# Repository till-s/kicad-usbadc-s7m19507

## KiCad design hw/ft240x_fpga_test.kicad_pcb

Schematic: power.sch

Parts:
C1, C2, C3, C7, C8, C14, C16, C17, C63: 10u; C_1206_3216Metric; Part CNC5L1X7R1C106K160AE
C4, C5, C6: 6p8; C_0603_1608Metric; Part 885012006050
C9, C12, C13, C15, C100, C101: 100n; C_0603_1608Metric; Part GCJ188R71E104KA12D
C10, C11: 47p; C_0603_1608Metric; Part 885012006055
D7: CTS05S30; sod323; Part CTS05S30
D8: CTS05S30; sod323-special; Part CTS05S30
FB1, FB3, FB4, FB5: Ferrite_Bead MPZ1608S221A; L_0603_1608Metric; Part MPZ1608S221ATA00
J1: Ext_Power; USB_Micro-B_Molex-105017-0001; Part 1050170001
J2: USB_C_Receptacle_USB2.0; USB_C_Receptacle_GCT_USB4085_smaller_holes
J3: Jtag_Master; PinHeader_1x04_P2.54mm_Vertical
J9: Expansion; PinHeader_2x04_P2.54mm_Vertical
J11: PEN_SEL; PinHeader_2x03_P2.54mm_Vertical
JP1: Jumper_2_Open; PinHeader_1x02_P2.54mm_Vertical
JP2: Jumper_ExtSup; PinHeader_1x03_P2.54mm_Vertical
JP3: Jumper_JTAG_hack; PinHeader_1x03_P2.54mm_Vertical
L1, L3: 2u2; L_Taiyo-Yuden_NR-50xx; Part SRN8040TA-2R2Y
L2: 2.2u; L_Taiyo-Yuden_NR-50xx+bourns0703; Part SRF0703-2R2M
NT1, NT2, NT3: Net-Tie_2; NetTie-2_SMD_Pad0.5mm
Q1, Q2: Si3477; TSOT-23-6; Part Si3477
R1, R2, R3, R4, R5, R8, R9, R71, R72, R73: 100k; R_0603_1608Metric; Part RC0603FR-07100KL
R6: 200k; R_0603_1608Metric; Part ERJ-3EKF2003V
R7: 316k; R_0603_1608Metric; Part RC0603FR-07316KL
R10: 47k; R_0603_1608Metric; Part RC0603FR-07100KL
R11, R12: 27; R_0603_1608Metric; Part RC0603FR-0727RL
R29: 50; R_0402_1005Metric
R63, R64, R67, R68: 10k; R_0603_1608Metric
R65, R66, R69: 5k1; R_0603_1608Metric
R70: 35k7; R_0603_1608Metric
U1, U2, U3: TLV62569DDC; SOT-23-6; Part TLV62569PDDC
U4: FT240XS; SSOP-24_3.9x8.7mm_P0.635mm; Part FT240XS-U
U15: UTC2000; QFN-16-1EP_3x3mm_P0.5mm_EP1.75x1.75mm_ThermalVias; Part UTC2000
U16: 74LVC1G32; SOT-353_SC-70-5

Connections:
+1V2: C6.1, C16.1, C17.1, L3.1, R8.2; also elsewhere on the board
+1V8_analog: FB4.2; also elsewhere on the board
+1V8_perm: C4.1, C7.1, C9.2, JP3.1 (A), L1.1, Q1.4 (S), R6.1
+2V5: C5.1, C8.1, D8.1 (K), FB3.1, J9.6, R7.1; also elsewhere on the board
+2V5_analog: FB3.2; also elsewhere on the board
+5V: C1.1, C2.1, C3.1, C14.1, C15.2, C101.2, J9.8, JP2.2 (C), Q2.4 (S), R1.1, R71.2, U1.1 (EN), U1.4 (VIN), U2.4 (VIN), U3.4 (VIN), U4.18 (VCC), U16.5 (VCC); also elsewhere on the board
-2V5: FB5.2; also elsewhere on the board
/Power/1A5: J11.2, U15.9 (1.5A#)
/Power/3A0: J11.4, U15.10 (3A#)
/Power/PWR_EN: R72.2, R73.2, U16.4
/Power/USBD_N: R12.2, U4.14 (USBDM)
/Power/USBD_P: R11.2, U4.13 (USBDP)
/Power/USBin_N: C11.1, J2.A7 (D-), J2.B7 (D-), R12.1
/Power/USBin_P: C10.2, J2.A6 (D+), J2.B6 (D+), R11.1
EXP_IO2_1V8: J9.5; also elsewhere on the board
FIFO_CLK: R29.2; also elsewhere on the board
FIFO_D0: U4.24 (DATA0); also elsewhere on the board
FIFO_D1: U4.4 (DATA1); also elsewhere on the board
FIFO_D2: J3.3, U4.2 (DATA2); also elsewhere on the board
FIFO_D3: J3.1, U4.9 (DATA3); also elsewhere on the board
FIFO_D4: J3.4, U4.1 (DATA4); also elsewhere on the board
FIFO_D5: J3.2, U4.7 (DATA5); also elsewhere on the board
FIFO_D6: U4.8 (DATA6); also elsewhere on the board
FIFO_D7: U4.5 (DATA7); also elsewhere on the board
FIFO_RDb: U4.11 (~RD); also elsewhere on the board
FIFO_RXE: U4.21 (~RXF); also elsewhere on the board
FIFO_SIWU: U4.10 (~SI/WU); also elsewhere on the board
FIFO_TXF: U4.20 (~TXE); also elsewhere on the board
FIFO_WRb: U4.12 (~WR); also elsewhere on the board
unnamed: C4.2, R2.1, R6.2, U1.6 (FB)
unnamed: C5.2, R3.1, R7.2, U2.6 (FB)
unnamed: C6.2, R4.1, R8.1, U3.6 (FB)
unnamed: C9.1, Q1.3 (G), R72.1
unnamed: C12.2, JP3.3 (B), U4.15 (3V3OUT), U4.16 (~RESET)
unnamed: C13.2, JP3.2 (C), U4.3 (VCCIO)
unnamed: C101.1, Q2.3 (G), R73.1
unnamed: D7.1 (K), L2.1
unnamed: D8.2 (A), L2.4
unnamed: FB1.1, Q2.1 (D), Q2.2 (D), Q2.5 (D), Q2.6 (D)
unnamed: J1.1 (VBUS), JP2.1 (A)
unnamed: J2.A5 (CC1), R64.1, R66.1
unnamed: J2.B5 (CC2), R63.1, R65.1
unnamed: J11.1, J11.3, J11.5, R71.1, U16.1
unnamed: JP1.2 (B), R9.1, U16.2
unnamed: L1.2, U1.3 (SW)
unnamed: L2.2, U2.3 (SW)
unnamed: L3.2, U3.3 (SW)
unnamed: NT1.1, R2.2
unnamed: NT2.1, R3.2
unnamed: NT3.1, R4.2
unnamed: R1.2, U2.5 (PG), U3.1 (EN)
unnamed: R5.1, U1.5 (PG), U2.1 (EN)
unnamed: R9.2, R10.2, U4.23 (CBUS5)
unnamed: R29.1, U4.22 (CBUS6)
unnamed: R63.2, U15.6 (CC2)
unnamed: R64.2, U15.7 (CC1)
unnamed: R67.2, U15.3 (Enable)
unnamed: R68.2, U15.2 (CFG_SEL)
unnamed: R69.1, R70.2, U15.12 (VMON)
VBUS: C100.1, J2.A4 (VBUS), J2.A9 (VBUS), J2.B4 (VBUS), J2.B9 (VBUS), JP2.3 (B), R10.1, R67.1, R68.1, R70.1, U15.16 (VDD)
Vpp_analog: FB1.2; also elsewhere on the board

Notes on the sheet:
For external supply: - jumper ext-power to +5V - jumper gate to GND - CBUS programmed to VBUS_SENSE For bus-power: - jumper VBUS to +5V - open gate jumper - CBUS programmed to #PWREN
Alt Inductor (not same footprint): Taiyo Yuden NRS5030T2R2NMGJ
Diode in the positive 2V5 branch is not necessary for switching but compensates the voltage drop of the respective diode in the (unregulated) negative -2V5 branch.

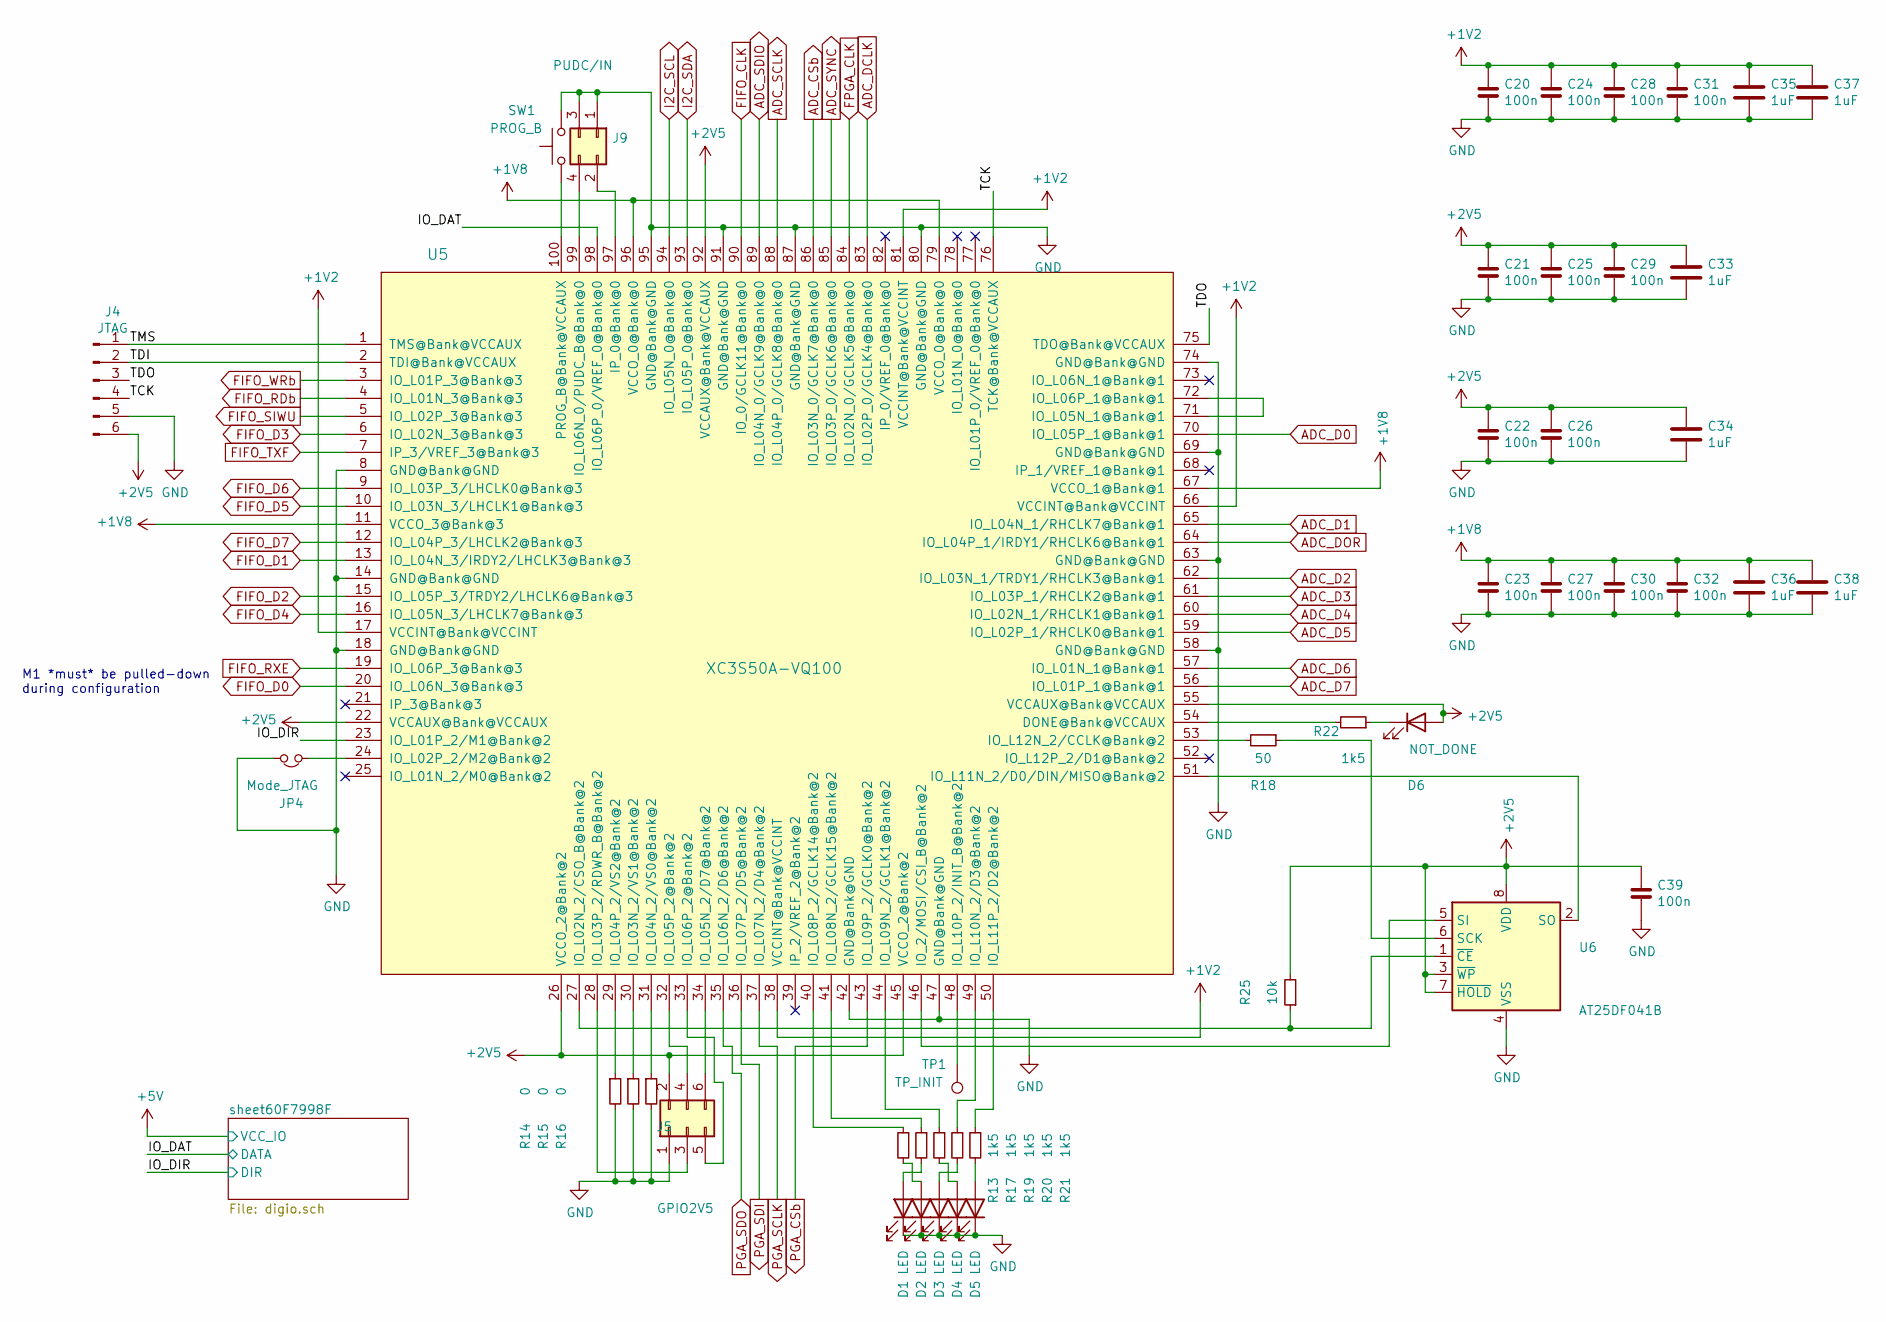
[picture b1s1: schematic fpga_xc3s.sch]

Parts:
C20, C21, C22, C23, C24, C25, C26, C27, C28, C29, C30, C31, C32, C39: 100n; C_0402_1005Metric; Part GRM155R61C104KA88D
C33, C34, C35, C36, C37, C38: 1uF; C_0805_2012Metric; Part GCJ219R71C105KA01
D1, D2, D3, D4, D5, D6: LED; LED_0603_1608Metric; Part 150060RS75000
J4: JTAG; PinHeader_1x06_P2.54mm_Vertical
J5: GPIO2V5; PinHeader_2x03_P2.54mm_Vertical
J9: PUDC/IN; PinHeader_2x02_P2.54mm_Vertical
JP4: Mode_JTAG; PinHeader_1x02_P2.54mm_Vertical
R13, R17, R19, R20, R21, R22: 1k5; R_0603_1608Metric; Part RC0603FR-071K5L
R14, R15, R16: 0; R_0603_1608Metric; Part RMCF0603ZT0R00
R18: 50; R_0603_1608Metric
R25: 10k; R_0603_1608Metric; Part RT0603FRE0710KL
SW1: PROG_B; SW_SPST_PTS810
TP1: TP_INIT; TestPoint_Pad_D1.0mm
U5: XC3S50A-VQ100; VQFP-100_14x14mm_P0.5mm
U6: AT25DF041B; SOIC-8_3.9x4.9mm_P1.27mm; Part AT25DF041B

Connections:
+1V2: C20.1, C24.1, C28.1, C31.1, C35.1, C37.1, U5.17 (VCCINT@Bank@VCCINT), U5.38 (VCCINT@Bank@VCCINT), U5.66 (VCCINT@Bank@VCCINT), U5.81 (VCCINT@Bank@VCCINT); also elsewhere on the board
+2V5: C21.1, C22.1, C25.1, C26.1, C29.1, C33.1, C34.1, C39.1, D6.2 (A), J4.6, J5.2, J9.6, R25.2, U5.22 (VCCAUX@Bank@VCCAUX), U5.26 (VCCO_2@Bank@2), U5.45 (VCCO_2@Bank@2), U5.55 (VCCAUX@Bank@VCCAUX), U5.92 (VCCAUX@Bank@VCCAUX), U6.3 (~WP~), U6.7 (~HOLD~), U6.8 (VDD); also elsewhere on the board
+5V: J9.8; also elsewhere on the board
/fpga_xc3s/IO_DAT: U5.98 (IO_L06P_0/VREF_0@Bank@0); also elsewhere on the board
/fpga_xc3s/LED_FRONT_G: U5.52 (IO_L12P_2/D1@Bank@2); also elsewhere on the board
/fpga_xc3s/TCK: J4.4, U5.76 (TCK@Bank@VCCAUX)
/fpga_xc3s/TDI: J4.2, U5.2 (TDI@Bank@VCCAUX)
/fpga_xc3s/TDO: J4.3, U5.75 (TDO@Bank@VCCAUX)
/fpga_xc3s/TMS: J4.1, U5.1 (TMS@Bank@VCCAUX)
ADC_CSb: U5.86 (IO_L03N_0/GCLK7@Bank@0); also elsewhere on the board
ADC_D0: U5.70 (IO_L05P_1@Bank@1); also elsewhere on the board
ADC_D1: U5.65 (IO_L04N_1/RHCLK7@Bank@1); also elsewhere on the board
ADC_D2: U5.62 (IO_L03N_1/TRDY1/RHCLK3@Bank@1); also elsewhere on the board
ADC_D3: U5.61 (IO_L03P_1/RHCLK2@Bank@1); also elsewhere on the board
ADC_D4: U5.60 (IO_L02N_1/RHCLK1@Bank@1); also elsewhere on the board
ADC_D5: U5.59 (IO_L02P_1/RHCLK0@Bank@1); also elsewhere on the board
ADC_D6: U5.57 (IO_L01N_1@Bank@1); also elsewhere on the board
ADC_D7: U5.56 (IO_L01P_1@Bank@1); also elsewhere on the board
ADC_DCLK: U5.83 (IO_L02P_0/GCLK4@Bank@0); also elsewhere on the board
ADC_DOR: U5.64 (IO_L04P_1/IRDY1/RHCLK6@Bank@1); also elsewhere on the board
ADC_SCLK: U5.88 (IO_L04P_0/GCLK8@Bank@0); also elsewhere on the board
ADC_SDIO: U5.89 (IO_L04N_0/GCLK9@Bank@0); also elsewhere on the board
ADC_SYNC: U5.85 (IO_L03P_0/GCLK6@Bank@0); also elsewhere on the board
EXP_IO2_1V8: J9.5, U5.78 (IO_L01N_0@Bank@0)
FIFO_CLK: U5.90 (IO_0/GCLK11@Bank@0); also elsewhere on the board
FIFO_D0: U5.20 (IO_L06N_3@Bank@3); also elsewhere on the board
FIFO_D1: U5.13 (IO_L04N_3/IRDY2/LHCLK3@Bank@3); also elsewhere on the board
FIFO_D2: U5.15 (IO_L05P_3/TRDY2/LHCLK6@Bank@3); also elsewhere on the board
FIFO_D3: U5.6 (IO_L02N_3@Bank@3); also elsewhere on the board
FIFO_D4: U5.16 (IO_L05N_3/LHCLK7@Bank@3); also elsewhere on the board
FIFO_D5: U5.10 (IO_L03N_3/LHCLK1@Bank@3); also elsewhere on the board
FIFO_D6: U5.9 (IO_L03P_3/LHCLK0@Bank@3); also elsewhere on the board
FIFO_D7: U5.12 (IO_L04P_3/LHCLK2@Bank@3); also elsewhere on the board
FIFO_RDb: U5.4 (IO_L01N_3@Bank@3); also elsewhere on the board
FIFO_RXE: U5.19 (IO_L06P_3@Bank@3); also elsewhere on the board
FIFO_SIWU: U5.5 (IO_L02P_3@Bank@3); also elsewhere on the board
FIFO_TXF: U5.7 (IP_3/VREF_3@Bank@3); also elsewhere on the board
FIFO_WRb: U5.3 (IO_L01P_3@Bank@3); also elsewhere on the board
FPGA_CLK: U5.84 (IO_L02N_0/GCLK5@Bank@0); also elsewhere on the board
I2C_SCL: U5.94 (IO_L05N_0@Bank@0); also elsewhere on the board
I2C_SDA: U5.93 (IO_L05P_0@Bank@0); also elsewhere on the board
unnamed: D1.2 (A), R17.2
unnamed: D2.2 (A), R13.2
unnamed: D3.2 (A), R20.2
unnamed: D4.2 (A), R19.2
unnamed: D5.2 (A), R21.2
unnamed: D6.1 (K), R22.1
unnamed: J5.3, U5.28 (IO_L03P_2/RDWR_B@Bank@2)
unnamed: J5.4, U5.32 (IO_L05P_2@Bank@2)
unnamed: J5.5, U5.33 (IO_L06P_2@Bank@2)
unnamed: J5.6, U5.34 (IO_L05N_2/D7@Bank@2)
unnamed: JP4.1, U5.24 (IO_L02P_2/M2@Bank@2)
unnamed: R13.1, U5.40 (IO_L08P_2/GCLK14@Bank@2)
unnamed: R14.1, U5.29 (IO_L04P_2/VS2@Bank@2)
unnamed: R15.1, U5.30 (IO_L03N_2/VS1@Bank@2)
unnamed: R16.1, U5.31 (IO_L04N_2/VS0@Bank@2)
unnamed: R17.1, U5.41 (IO_L08N_2/GCLK15@Bank@2)
unnamed: R18.1, U6.6 (SCK)
unnamed: R18.2, U5.53 (IO_L12N_2/CCLK@Bank@2)
unnamed: R19.1, U5.44 (IO_L09N_2/GCLK1@Bank@2)
unnamed: R20.1, U5.49 (IO_L10N_2/D3@Bank@2)
unnamed: R21.1, U5.50 (IO_L11P_2/D2@Bank@2)
unnamed: R22.2, U5.54 (DONE@Bank@VCCAUX)
unnamed: R25.1, U5.27 (IO_L02N_2/CSO_B@Bank@2), U6.1 (~CE)
unnamed 158: U5.25 (IO_L01N_2/M0@Bank@2); also elsewhere on the board
unnamed: SW1.1, U5.100 (PROG_B@Bank@VCCAUX)
unnamed: TP1.1, U5.48 (IO_L10P_2/INIT_B@Bank@2)
unnamed: U5.46 (IO_2/MOSI/CSI_B@Bank@2), U6.5 (SI)
unnamed: U5.51 (IO_L11N_2/D0/DIN/MISO@Bank@2), U6.2 (SO)
PGA_CSb: U5.43 (IO_L09P_2/GCLK0@Bank@2); also elsewhere on the board
PGA_SCLK: U5.37 (IO_L07N_2/D4@Bank@2); also elsewhere on the board
PGA_SDI: U5.36 (IO_L07P_2/D5@Bank@2); also elsewhere on the board
PGA_SDO: U5.35 (IO_L06N_2/D6@Bank@2); also elsewhere on the board

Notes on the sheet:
M1 *must* be pulled-down during configuration

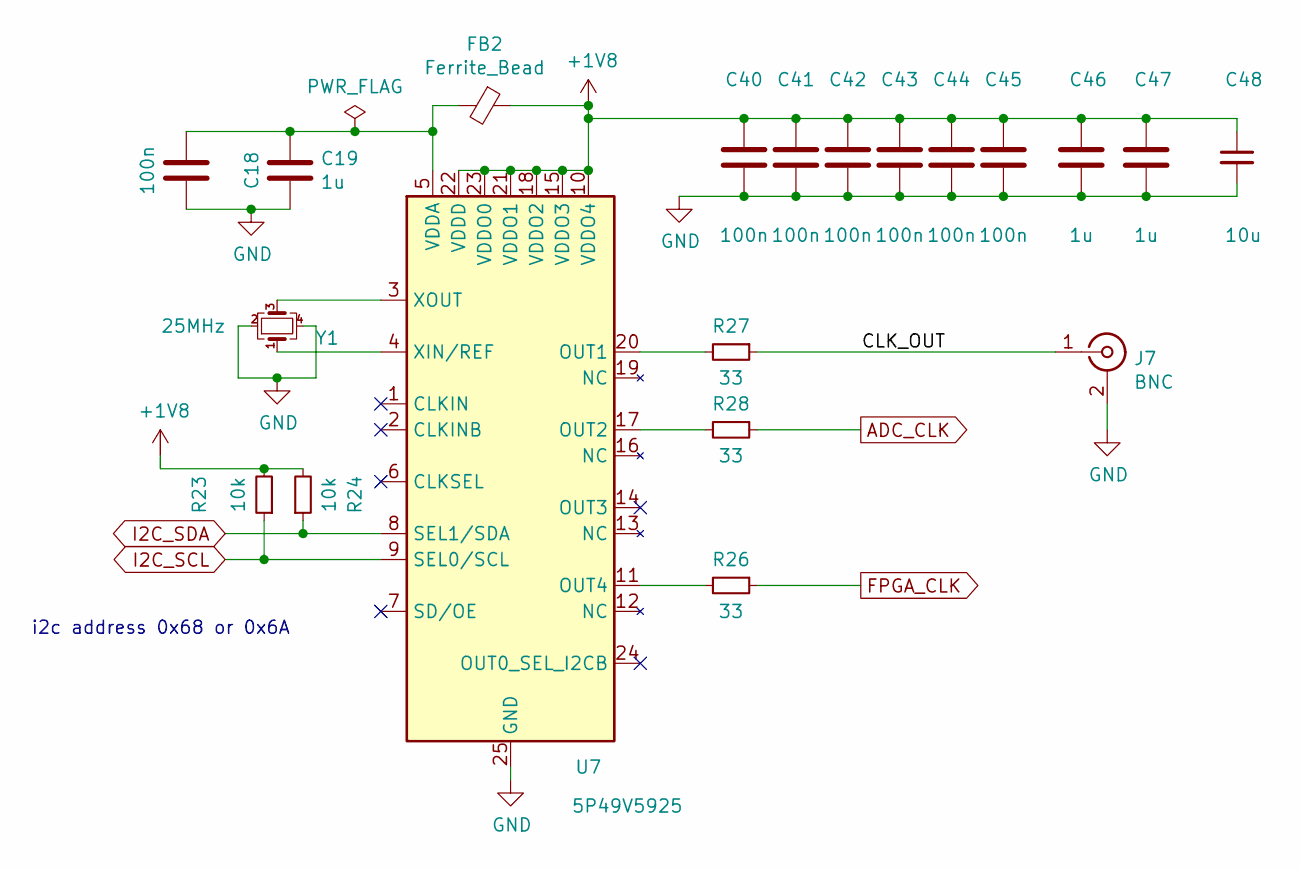
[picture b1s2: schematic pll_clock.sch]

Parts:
C18, C40, C41, C42, C43, C44, C45: 100n; C_0603_1608Metric; Part GCJ188R71E104KA12D
C19, C46, C47: 1u; C_0805_2012Metric; Part GCJ219R71C105KA01
C48: 10u; C_1206_3216Metric; Part CNC5L1X7R1C106K160AE
FB2: Ferrite_Bead; L_0603_1608Metric; Part MPZ1608S221ATA00
J7: BNC; BNC_Molex_0731713150; Part 0731713150
R23, R24: 10k; R_0603_1608Metric; Part RT0603FRE0710KL
R26, R27, R28: 33; R_0603_1608Metric; Part RC0603FR-0733RL
U7: 5P49V5925; QFN-24-1EP_4x4mm_P0.5mm_EP2.8x2.8mm; Part 5P49V5925
Y1: 25MHz; Crystal_SMD_Abracon_ABM10-4Pin_2.5x2.0mm; Part ABM10W-25.0000MHZ-8-B1U-T3

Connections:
/pll_clock/CLK_OUT: J7.1 (In), R27.1
ADC_CLK: R28.1; also elsewhere on the board
FPGA_CLK: R26.1; also elsewhere on the board
I2C_SCL: R23.1, U7.9 (SEL0/SCL); also elsewhere on the board
I2C_SDA: R24.1, U7.8 (SEL1/SDA); also elsewhere on the board
unnamed: C18.2, C19.1, FB2.2, U7.5 (VDDA)
unnamed: R26.2, U7.11 (OUT4)
unnamed: R27.2, U7.20 (OUT1)
unnamed: R28.2, U7.17 (OUT2)
unnamed 161: U7.24 (OUT0_SEL_I2CB); also elsewhere on the board
unnamed: U7.3 (XOUT), Y1.3
unnamed: U7.4 (XIN/REF), Y1.1

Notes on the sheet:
i2c address 0x68 or 0x6A

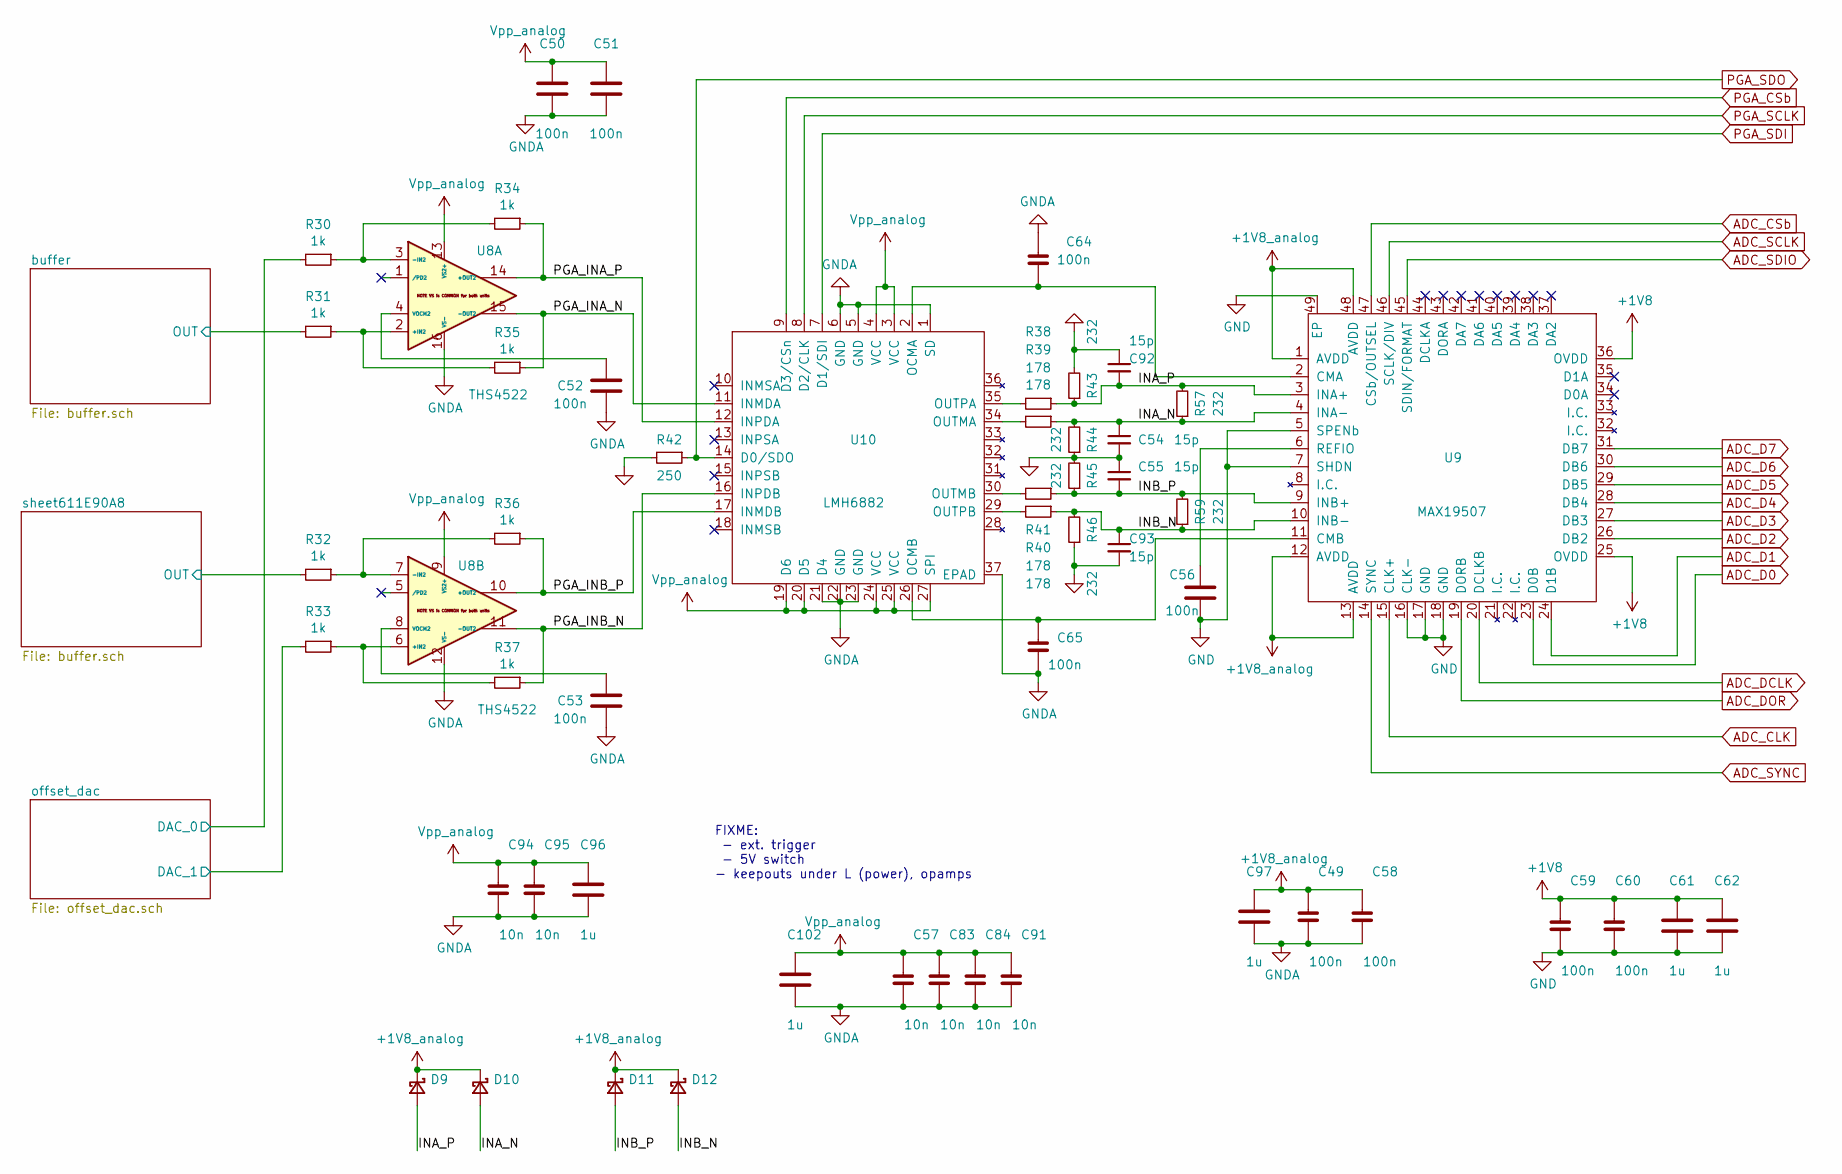
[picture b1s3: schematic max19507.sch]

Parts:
C49, C58, C59, C60, C64, C65: 100n; C_0402_1005Metric; Part GRM155R61C104KA88D
C50, C51, C52, C53, C56: 100n; C_0603_1608Metric; Part GCJ188R71E104KA12D
C54, C55, C92, C93: 15p; C_0603_1608Metric
C57, C83, C84, C91, C94, C95: 10n; C_0402_1005Metric; Part GRM155R61C103KA01
C61, C62, C96, C97, C102: 1u; C_0805_2012Metric; Part GCJ219R71C105KA01
D9, D10, D11, D12: NSR0170HT1G; D_SOD-323; Part NSR0170HT1G
R30, R31, R32, R33, R34, R35, R36, R37: 1k; R_0603_1608Metric
R38, R39, R40, R41: 178; R_0603_1608Metric
R42: 250; R_0603_1608Metric
R43, R44, R45, R46, R57, R59: 232; R_0603_1608Metric
U8: THS4522; TSSOP-16_4.4x5mm_P0.65mm
U9: MAX19507; TQFP-48-1EP_7x7mm_P0.5mm_EP5x5mm_ThermalVias
U10: LMH6882; Texas_S-PVQFN-N36_EP4.4x4.4mm_ThermalVias; Part LMH6882

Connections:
+1V8_analog: C49.1, C58.1, C97.1, D9.1 (K), D10.1 (K), D11.1 (K), D12.1 (K), U9.1 (AVDD), U9.12 (AVDD), U9.13 (AVDD), U9.48 (AVDD); also elsewhere on the board
/ADC+Driver/INA_N: C54.1, D10.2 (A), R39.1, R44.2, R57.1, U9.4 (INA-)
/ADC+Driver/INA_P: C92.2, D9.2 (A), R38.1, R43.1, R57.2, U9.3 (INA+)
/ADC+Driver/INB_N: C93.1, D12.2 (A), R41.1, R46.2, R59.1, U9.10 (INB-)
/ADC+Driver/INB_P: C55.2, D11.2 (A), R40.1, R45.1, R59.2, U9.9 (INB+)
/ADC+Driver/PGA_INA_N: R35.1, U8.15 (-OUT2), U10.11 (INMDA)
/ADC+Driver/PGA_INA_P: R34.1, U8.14 (+OUT2), U10.12 (INPDA)
/ADC+Driver/PGA_INB_N: R37.1, U8.11 (-OUT2), U10.16 (INPDB)
/ADC+Driver/PGA_INB_P: R36.1, U8.10 (+OUT2), U10.17 (INMDB)
/ADC+Driver/buffer/OUT: R31.2; also elsewhere on the board
/ADC+Driver/offset_dac/DAC_0: R30.2; also elsewhere on the board
/ADC+Driver/offset_dac/DAC_1: R33.2; also elsewhere on the board
/ADC+Driver/sheet611E90A8/OUT: R32.2; also elsewhere on the board
ADC_CLK: U9.15 (CLK+); also elsewhere on the board
ADC_CSb: U9.47 (CSb/OUTSEL); also elsewhere on the board
ADC_D0: U9.23 (D0B); also elsewhere on the board
ADC_D1: U9.24 (D1B); also elsewhere on the board
ADC_D2: U9.26 (DB2); also elsewhere on the board
ADC_D3: U9.27 (DB3); also elsewhere on the board
ADC_D4: U9.28 (DB4); also elsewhere on the board
ADC_D5: U9.29 (DB5); also elsewhere on the board
ADC_D6: U9.30 (DB6); also elsewhere on the board
ADC_D7: U9.31 (DB7); also elsewhere on the board
ADC_DCLK: U9.20 (DCLKB); also elsewhere on the board
ADC_DOR: U9.19 (DORB); also elsewhere on the board
ADC_SCLK: U9.46 (SCLK/DIV); also elsewhere on the board
ADC_SDIO: U9.45 (SDIN/FORMAT); also elsewhere on the board
ADC_SYNC: U9.14 (SYNC); also elsewhere on the board
unnamed: C52.2, U8.4 (VOCM2)
unnamed: C53.2, U8.8 (VOCM2)
unnamed: C56.2, U9.6 (REFIO)
unnamed: C64.2, U9.2 (CMA), U10.2 (OCMA)
unnamed: C65.1, U9.11 (CMB), U10.26 (OCMB)
unnamed: R30.1, R34.2, U8.3 (-IN2)
unnamed: R31.1, R35.2, U8.2 (+IN2)
unnamed: R32.1, R36.2, U8.7 (-IN2)
unnamed: R33.1, R37.2, U8.6 (+IN2)
unnamed: R38.2, U10.35 (OUTPA)
unnamed: R39.2, U10.34 (OUTMA)
unnamed: R40.2, U10.30 (OUTMB)
unnamed: R41.2, U10.29 (OUTPB)
PGA_CSb: U10.9 (D3/CSn); also elsewhere on the board
PGA_SCLK: U10.8 (D2/CLK); also elsewhere on the board
PGA_SDI: U10.7 (D1/SDI); also elsewhere on the board
PGA_SDO: R42.1, U10.14 (D0/SDO); also elsewhere on the board
Vpp_analog: C50.2, C51.2, C57.1, C83.1, C84.1, C91.1, C94.1, C95.1, C96.1, C102.1, U8.9 (VS2+), U8.13 (VS2+), U10.3 (VCC), U10.4 (VCC), U10.19 (D6), U10.20 (D5), U10.24 (VCC), U10.25 (VCC), U10.27 (SPI); also elsewhere on the board

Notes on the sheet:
FIXME: - ext. trigger - 5V switch - keepouts under L (power), opamps

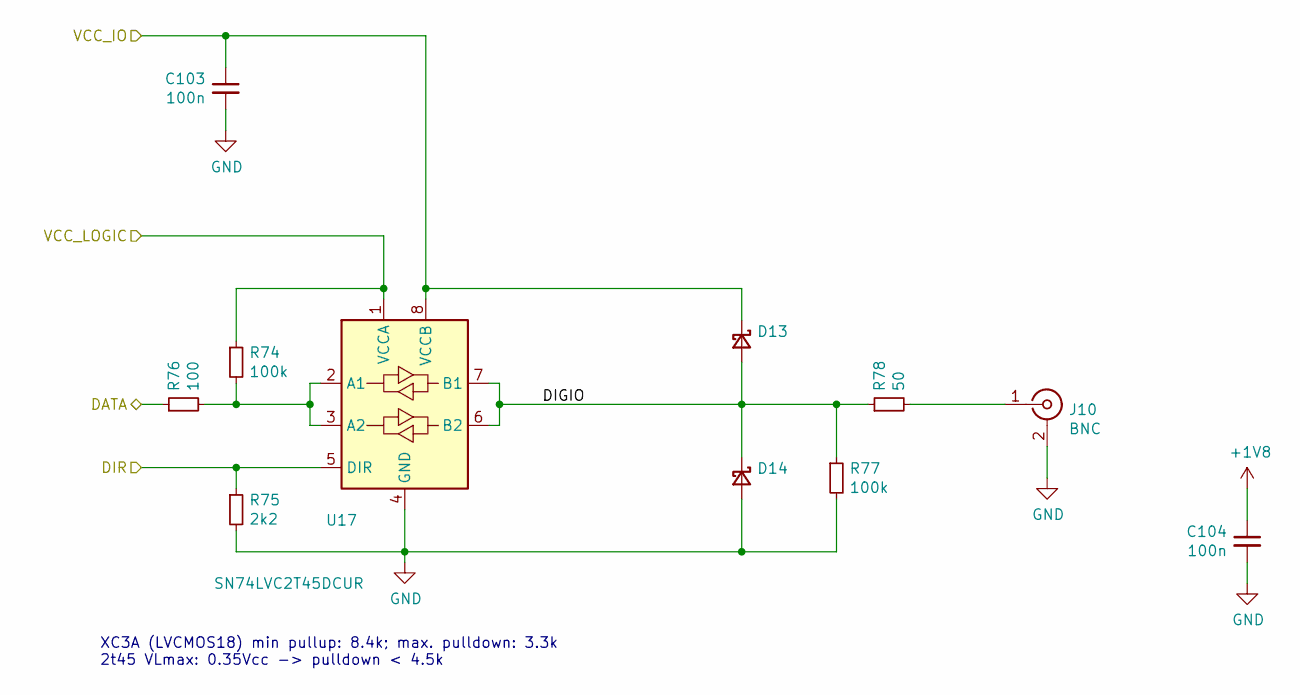
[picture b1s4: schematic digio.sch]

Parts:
C2001, C2002: 100n; C_0402_1005Metric
D13, D14: NSR0170HT1G; D_SOD-323; Part NSR0170HT1G
J2001: BNC; BNC_Molex_0731713150; Part 0731713150
R2001, R2005: 100k; R_0603_1608Metric
R2002: 2k2; R_0603_1608Metric
R2003: 100; R_0603_1608Metric
R2004: 50; R_0603_1608Metric
U17: SN74LVC2T45DCUR; VSSOP-8_2.4x2.1mm_P0.5mm

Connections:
+5V: D13.1 (K), U17.8 (VCCB); also elsewhere on the board
/fpga_xc3s/sheet60F7998F/DIGIO: D13.2 (A), D14.1 (K), U17.6 (B2), U17.7 (B1); also elsewhere on the board
unnamed 157: U17.2 (A1), U17.3 (A2); also elsewhere on the board

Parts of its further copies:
C103, C104, C2051, C2052: 100n; C_0402_1005Metric
J10, J2051: BNC; BNC_Molex_0731713150; Part 0731713150
R74, R77, R2051, R2055: 100k; R_0603_1608Metric
R75, R2052: 2k2; R_0603_1608Metric
R76, R2053: 100; R_0603_1608Metric
R2054: 50; R_0603_1608Metric

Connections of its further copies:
+5V: C103.1; also elsewhere on the board
/fpga_xc3s/IO_DAT: R76.1; also elsewhere on the board
/fpga_xc3s/sheet60F7998F/DIGIO: R77.1; also elsewhere on the board
unnamed 157: R74.2, R76.2; also elsewhere on the board

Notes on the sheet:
XC3A (LVCMOS18) min pullup: 8.4k; max. pulldown: 3.3k 2t45 VLmax: 0.35Vcc -> pulldown < 4.5k

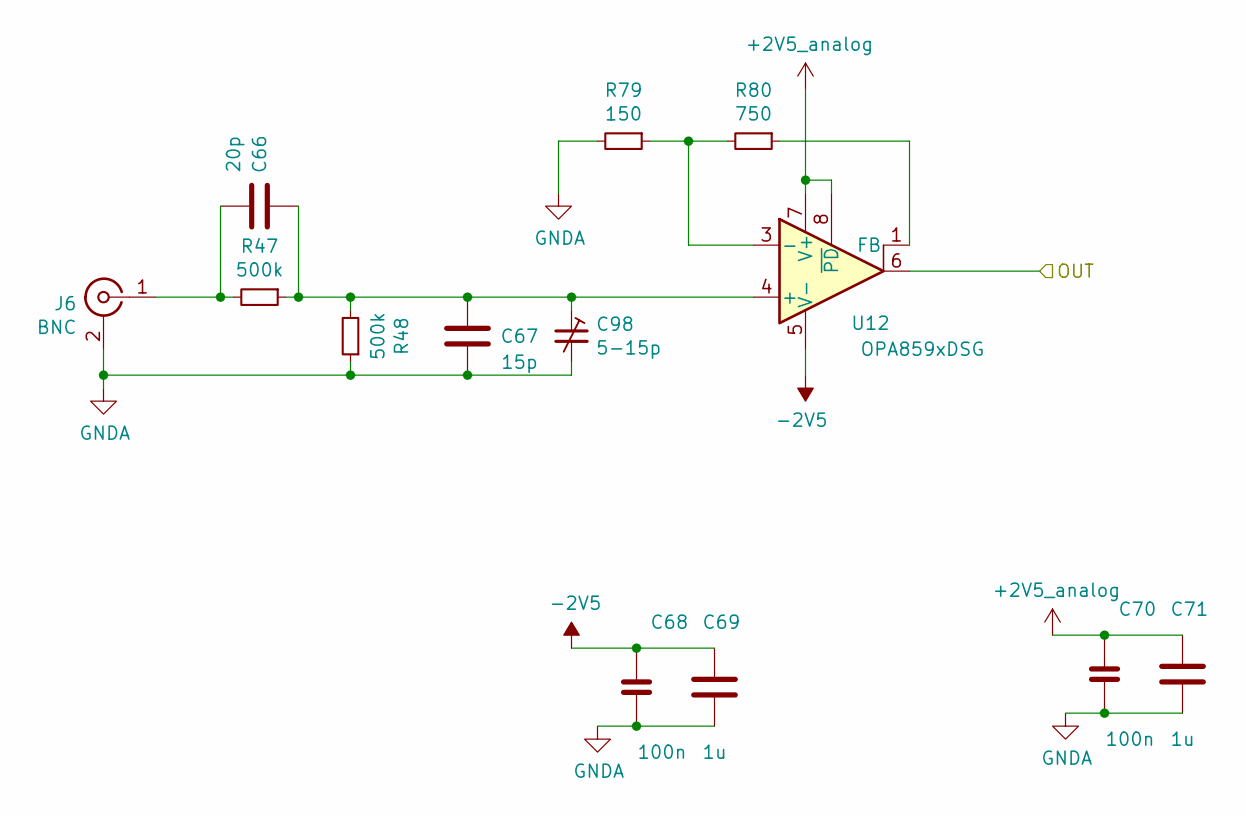
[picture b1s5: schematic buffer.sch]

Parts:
C66: 20p; C_0603_1608Metric
C67: 15p; C_0603_1608Metric
C68, C70: 100n; C_0402_1005Metric; Part GRM155R61C104KA88D
C69, C71: 1u; C_0805_2012Metric; Part GCJ219R71C105KA01
C98: 5-15p; C_Trimmer_EW_Electronics_SCG3S
J6: BNC; BNC_Molex_0731713150; Part 0731713150
R47, R48: 500k; R_0603_1608Metric
R81: 150; R_0402_1005Metric
R82: 750; R_0402_1005Metric
U12: OPA859xDSG; WSON-8-1EP_2x2mm_P0.5mm_EP0.9x1.6mm

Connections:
+2V5_analog: C70.1, C71.1, U12.7 (V+), U12.8 (~PD); also elsewhere on the board
-2V5: C68.1, C69.1, U12.5 (V-), U12.9 (V-); also elsewhere on the board
/ADC+Driver/buffer/OUT: U12.6; also elsewhere on the board
unnamed: C66.1, J6.1 (In), R47.2
unnamed: C66.2, C67.2, C98.1, R47.1, R48.2, U12.4 (+)

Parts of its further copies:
C72: 20p; C_0603_1608Metric
C73: 15p; C_0603_1608Metric
C74, C76: 100n; C_0402_1005Metric; Part GRM155R61C104KA88D
C75, C77: 1u; C_0805_2012Metric; Part GCJ219R71C105KA01
C99: 5-15p; C_Trimmer_EW_Electronics_SCG3S
J8: BNC; BNC_Molex_0731713150; Part 0731713150
R49, R50: 500k; R_0603_1608Metric
R79: 150; R_0402_1005Metric
R80: 750; R_0402_1005Metric
U13: OPA859xDSG; WSON-8-1EP_2x2mm_P0.5mm_EP0.9x1.6mm

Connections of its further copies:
+2V5_analog: C76.1, C77.1, U13.7 (V+), U13.8 (~PD); also elsewhere on the board
-2V5: C74.1, C75.1, U13.5 (V-), U13.9 (V-); also elsewhere on the board
/ADC+Driver/sheet611E90A8/OUT: U13.6; also elsewhere on the board
unnamed: C72.1, J8.1 (In), R49.2
unnamed: C72.2, C73.2, C99.1, R49.1, R50.2, U13.4 (+)

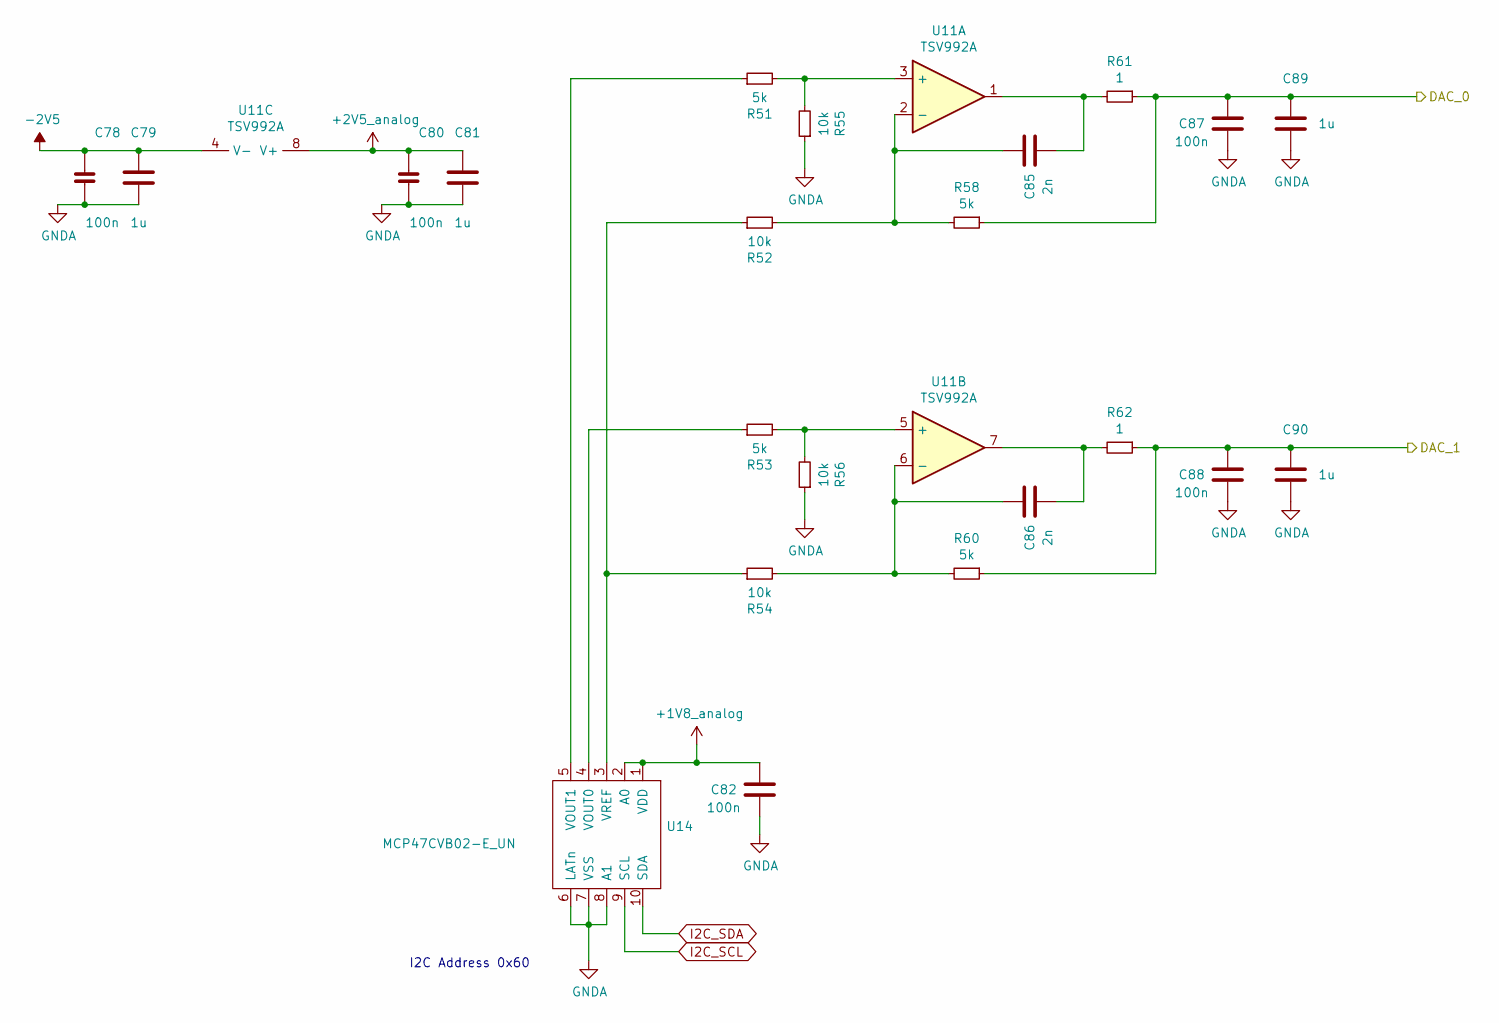
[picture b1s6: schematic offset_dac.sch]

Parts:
C78, C80: 100n; C_0402_1005Metric; Part GRM155R61C104KA88D
C79, C81, C89, C90: 1u; C_0805_2012Metric; Part GCJ219R71C105KA01
C82, C87, C88: 100n; C_0603_1608Metric; Part GCJ188R71E104KA12D
C85, C86: 2n; C_0603_1608Metric
R51, R53, R58, R60: 5k; R_0603_1608Metric
R52, R54, R55, R56: 10k; R_0603_1608Metric
R61, R62: 1; R_0603_1608Metric
U11: TSV992A; DFN-8-1EP_2x2mm_P0.5mm_EP0.45x1.6mm
U14: MCP47CVB02-E_UN; MSOP-10_3x3mm_P0.5mm; Part MCP47CVB02-E_UN

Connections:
+1V8_analog: C82.2, U14.1 (VDD), U14.2 (A0); also elsewhere on the board
+2V5_analog: C80.1, C81.1, U11.8 (V+); also elsewhere on the board
-2V5: C78.1, C79.1, U11.4 (V-); also elsewhere on the board
/ADC+Driver/offset_dac/DAC_0: C87.2, C89.1, R58.1, R61.1; also elsewhere on the board
/ADC+Driver/offset_dac/DAC_1: C88.2, C90.1, R60.1, R62.1; also elsewhere on the board
I2C_SCL: U14.9 (SCL); also elsewhere on the board
I2C_SDA: U14.10 (SDA); also elsewhere on the board
unnamed: C85.1, R61.2, U11.1
unnamed: C85.2, R52.2, R58.2, U11.2 (-)
unnamed: C86.1, R62.2, U11.7
unnamed: C86.2, R54.2, R60.2, U11.6 (-)
unnamed: R51.1, U14.5 (VOUT1)
unnamed: R51.2, R55.2, U11.3 (+)
unnamed: R52.1, R54.1, U14.3 (VREF)
unnamed: R53.1, U14.4 (VOUT0)
unnamed: R53.2, R56.2, U11.5 (+)

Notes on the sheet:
I2C Address 0x60

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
